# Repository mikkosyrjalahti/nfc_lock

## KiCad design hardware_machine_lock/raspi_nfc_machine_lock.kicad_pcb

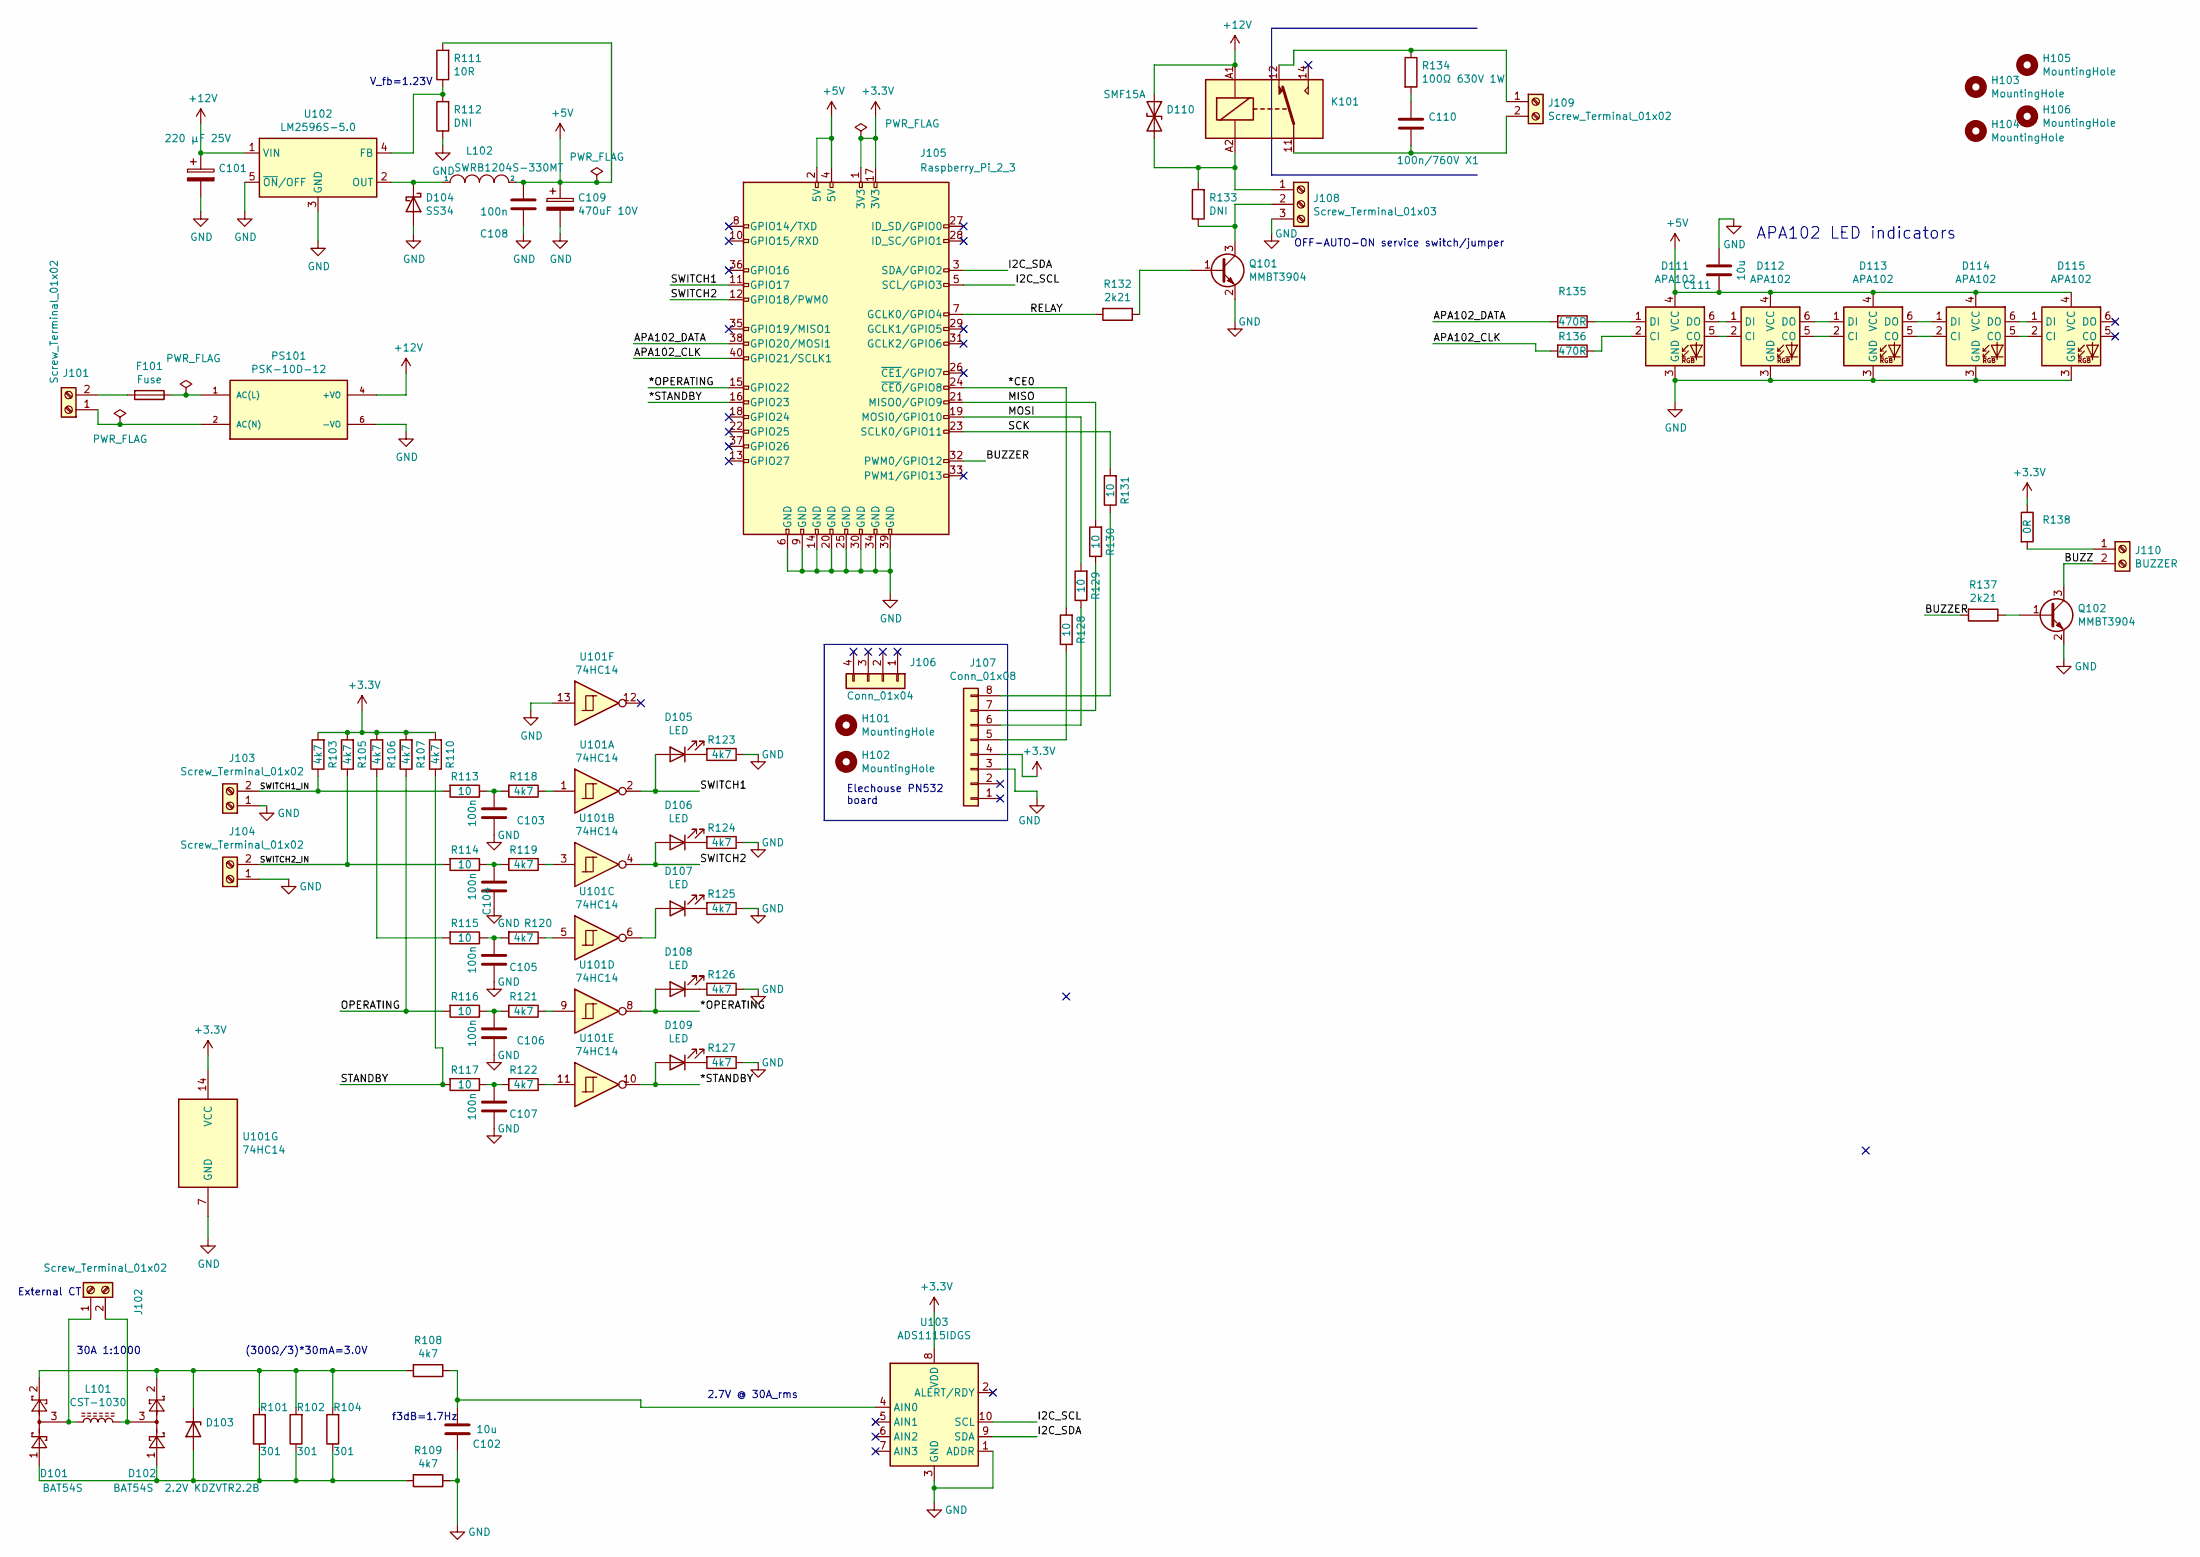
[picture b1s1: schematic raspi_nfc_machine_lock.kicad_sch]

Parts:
C101: 220 μF 25V; CP_Elec_8x10
C102, C111: 10u; C_0603
C103, C104, C105, C106, C107: 100n; C_0603
C108: 100n; C_1206
C109: 470uF 10V; CP_Elec_8x10.5
C110: 100n/760V X1; C_Rect_L18.0mm_W7.0mm_P15.00mm_FKS3_FKP3
D101, D102: BAT54S; SOT-23
D103: 2.2V KDZVTR2.2B; D_SOD-123F
D104: SS34; D_SMA
D105, D106, D107, D108, D109: LED; D_0603_1608Metric
D110: SMF15A; D_SOD-123
D111, D112, D113, D114, D115: APA102; LED_RGB_5050-6
F101: Fuse; Fuse_SMD2920
H101, H102: MountingHole; MountingHole_2.7mm_M2.5
H103, H104, H105, H106: MountingHole; MountingHole_3.2mm_M3
J101, J109: Screw_Terminal_01x02; TerminalBlock_bornier-2_P5.08mm
J102, J103, J104: Screw_Terminal_01x02; TerminalBlock_Phoenix_MPT-0,5-2-2.54_1x02_P2.54mm_Horizontal
J105: Raspberry_Pi_2_3; Pin_Header_Straight_2x20_Pitch2.54mm
J106: Conn_01x04; Pin_Header_Straight_1x04_Pitch2.54mm
J107: Conn_01x08; Pin_Header_Straight_1x08_Pitch2.54mm
J108: Screw_Terminal_01x03; TerminalBlock_bornier-3_P5.08mm
J110: BUZZER; TerminalBlock_Phoenix_MPT-0,5-2-2.54_1x02_P2.54mm_Horizontal
K101: (no value)
L101: CST-1030; AC1030
L102: SWRB1204S-330MT; L_12x12mm_H6mm
PS101: PSK-10D-12; CUI_PSK-10-D; PARTREV 1.0
Q101, Q102: MMBT3904; SOT-23
R101, R102, R104: 301; R_1206
R103, R105, R106, R107, R108, R109, R110, R118, R119, R120, R121, R122, R123, R124, R125, R126, R127: 4k7; R_0603
R111: 10R; R_0603
R112, R133: DNI; R_0603
R113, R114, R115, R116, R117, R128, R129, R130, R131: 10; R_0603
R132, R137: 2k21; R_0603
R134: 100Ω 630V 1W; R_Axial_DIN0411_L9.9mm_D3.6mm_P12.70mm_Horizontal
R135, R136: 470R; R_0603
R138: 0R; R_0603
U101: 74HC14; SOIC-14_3.9x8.7mm_P1.27mm
U102: LM2596S-5.0; TO-263-5_TabPin3
U103: ADS1115IDGS; TSSOP-10_3x3mm_P0.5mm

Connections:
+3V3: J105.1 (3V3), J105.17 (3V3), J107.4, R103.2, R105.2, R106.2, R107.2, R110.2, R138.1, U101.14 (VCC), U103.8 (VDD)
+5V: C108.2, C109.1, C111.1, D111.4 (VCC), D112.4 (VCC), D113.4 (VCC), D114.4 (VCC), D115.4 (VCC), J105.2 (5V), J105.4 (5V), L102.2, R111.2
+12V: C101.1, D110.1 (A1), K101.A1, PS101.4 (+VO), U102.1 (VIN)
/*CE0: J105.24 (~CE0/GPIO8), R128.2
/*OPERATING: D108.2 (A), J105.15 (GPIO22), U101.8
/*STANDBY: D109.2 (A), J105.16 (GPIO23), U101.10
/APA102_CLK: J105.40 (GPIO21/SCLK1), R136.2
/APA102_DATA: J105.38 (GPIO20/MOSI1), R135.2
/BUZZ: J110.2, Q102.3 (C)
/BUZZER: J105.32 (PWM0/GPIO12), R137.2
/I2C_SCL: J105.5 (SCL/GPIO3), U103.10 (SCL)
/I2C_SDA: J105.3 (SDA/GPIO2), U103.9 (SDA)
/MISO: J105.21 (MISO0/GPIO9), R130.2
/MOSI: J105.19 (MOSI0/GPIO10), R129.2
/OPERATING: R107.1, R116.2
/RELAY: J105.7 (GCLK0/GPIO4), R132.2
/SCK: J105.23 (SCLK0/GPIO11), R131.2
/STANDBY: R110.1, R117.2
/SWITCH1: D105.2 (A), J105.11 (GPIO17), U101.2
/SWITCH1_IN: J103.2, R103.1, R113.2
/SWITCH2: D106.2 (A), J105.12 (GPIO18/PWM0), U101.4
/SWITCH2_IN: J104.2, R105.1, R114.2
GND: C101.2, C102.1, C103.1, C104.1, C105.1, C106.1, C107.1, C108.1, C109.2, C111.2, D104.2 (A), D111.3 (GND), D112.3 (GND), D113.3 (GND), D114.3 (GND), D115.3 (GND), J103.1, J104.1, J105.6 (GND), J105.9 (GND), J105.14 (GND), J105.20 (GND), J105.25 (GND), J105.30 (GND), J105.34 (GND), J105.39 (GND), J107.3, J108.3, PS101.6 (-VO), Q101.2 (E), Q102.2 (E), R109.1, R112.1, R123.1, R124.1, R125.1, R126.1, R127.1, U101.7 (GND), U101.13, U102.3 (GND), U102.5 (~ON/OFF), U103.1 (ADDR), U103.3 (GND)
unnamed: C102.2, R108.1, U103.4 (AIN0)
unnamed: C103.2, R113.1, R118.2
unnamed: C104.2, R114.1, R119.2
unnamed: C105.2, R115.1, R120.2
unnamed: C106.2, R116.1, R121.2
unnamed: C107.2, R117.1, R122.2
unnamed: C110.1, R134.2
unnamed: C110.2, J109.2, K101.11
unnamed: D101.1, D102.1, D103.2 (A), R101.1, R102.1, R104.1, R109.2
unnamed: D101.2, D102.2, D103.1 (K), R101.2, R102.2, R104.2, R108.2
unnamed: D101.3, J102.1, L101.1
unnamed: D102.3, J102.2, L101.2
unnamed: D104.1 (K), L102.1, U102.2 (OUT)
unnamed: D105.1 (K), R123.2
unnamed: D106.1 (K), R124.2
unnamed: D107.1 (K), R125.2
unnamed: D107.2 (A), U101.6
unnamed: D108.1 (K), R126.2
unnamed: D109.1 (K), R127.2
unnamed: D110.2 (A2), J108.1, K101.A2, R133.2
unnamed: D111.1 (DI), R135.1
unnamed: D111.2 (CI), R136.1
unnamed: D111.5 (CO), D112.2 (CI)
unnamed: D111.6 (DO), D112.1 (DI)
unnamed: D112.5 (CO), D113.2 (CI)
unnamed: D112.6 (DO), D113.1 (DI)
unnamed: D113.5 (CO), D114.2 (CI)
unnamed: D113.6 (DO), D114.1 (DI)
unnamed: D114.5 (CO), D115.2 (CI)
unnamed: D114.6 (DO), D115.1 (DI)
unnamed: F101.1, PS101.1 (AC(L))
unnamed: F101.2, J101.2
unnamed: J101.1, PS101.2 (AC(N))
unnamed: J107.5, R128.1
unnamed: J107.6, R129.1
unnamed: J107.7, R130.1
unnamed: J107.8, R131.1
unnamed: J108.2, Q101.3 (C), R133.1
unnamed: J109.1, K101.12, R134.1
unnamed: J110.1, R138.2
unnamed: Q101.1 (B), R132.1
unnamed: Q102.1 (B), R137.1
unnamed: R106.1, R115.2
unnamed: R111.1, R112.2, U102.4 (FB)
unnamed: R118.1, U101.1
unnamed: R119.1, U101.3
unnamed: R120.1, U101.5
unnamed: R121.1, U101.9
unnamed: R122.1, U101.11

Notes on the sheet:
2.7V @ 30A_rms
V_fb=1.23V
30A 1:1000
APA102 LED indicators
(300Ω/3)*30mA=3.0V
OFF-AUTO-ON service switch/jumper
External CT
Elechouse PN532 board
f3dB=1.7Hz

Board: 2 copper layers, 91 parts (0 on the bottom side), 72 nets, no tracks yet.

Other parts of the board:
L103: 560n; R_0805

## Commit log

2021-07-24 WIP commit before removing PN532 and current comparators
2022-12-04 Update KiCad version
2023-01-16 WIP commit to share. PSK10D, relay and current transformer confirmed with a print
2024-11-24 Use systemctl to restart keyserver
